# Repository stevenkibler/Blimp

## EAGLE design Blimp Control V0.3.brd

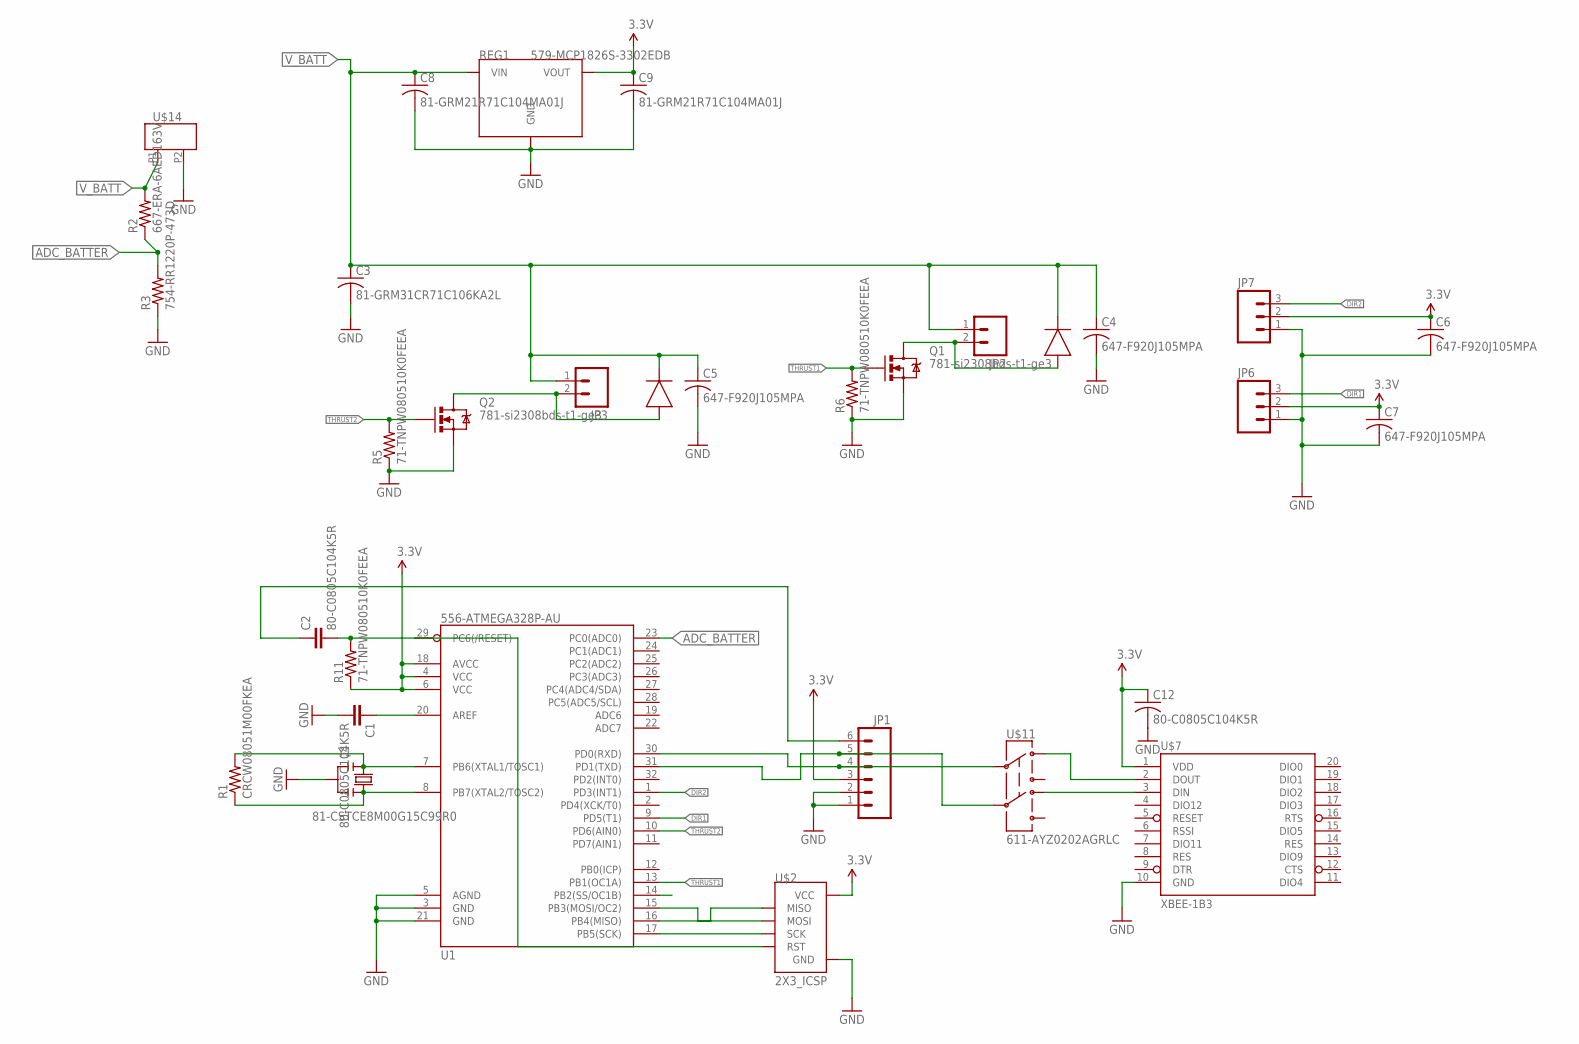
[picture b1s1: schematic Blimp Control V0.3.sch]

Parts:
C1, C2: 80-C0805C104K5R; 0805
C3: 81-GRM31CR71C106KA2L; C1206
C4, C5, C6, C7: 647-F920J105MPA; C0805
C8, C9: 81-GRM21R71C104MA01J; C0805
C12: 80-C0805C104K5R; C0805
D1, D2: 621-SBR07U20LPS-7; X2-DFN1006-2
JP1: M06LOCK; 1X06_LOCK
JP2, JP3: M02PTH; 1X02
JP6, JP7: M03LOCK; 1X03_LOCK
Q1, Q2: 781-si2308bds-t1-ge3; SOT23-3
R1: CRCW08051M00FKEA; 0805
R2: 667-ERA-6AED163V; R0805
R3: 754-RR1220P-473D; R0805
R5, R6: 71-TNPW080510K0FEEA; 0805
R11: 71-TNPW080510K0FEEA; R0805
REG1: 579-MCP1826S-3302EDB; SOT-223-3
U1: 556-ATMEGA328P-AU; TQFP32-08
U$2: 2X3_ICSP
U$7: XBEE-1B3; XBEE-SMD
U$11: 611-AYZ0202AGRLC; AYZ0202
U$14: 538-53047-0210; MOLEX_2POLE_PICO
Y1: 81-CSTCE8M00G15C99R0; RESONATOR

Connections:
3.3V: C6.1, C7.1, C9.1, C12.1, JP1.3, JP6.2, JP7.2, R11.1, REG1.3 (VOUT), U1.4 (VCC), U1.6 (VCC), U1.18 (AVCC), U$2.VCC, U$7.1 (VDD)
ADC_BATTER: R2.1, R3.2, U1.23 (PC0(ADC0))
ARDUINO_TX: JP1.5, U1.31 (PD1(TXD)), U$11.5
DIR1: JP6.3, U1.9 (PD5(T1))
DIR2: JP7.3, U1.1 (PD3(INT1))
GND: C1.2, C3.2, C4.2, C5.2, C6.2, C7.2, C8.2, C9.2, C12.2, JP1.1, JP1.2, JP6.1, JP7.1, Q1.2 (S), Q2.2 (S), R3.1, R5.1, R6.1, REG1.2 (GND), REG1.4 (GND), U1.3 (GND), U1.5 (AGND), U1.21 (GND), U$2.GND, U$7.10 (GND), U$14.P2, Y1.2
unnamed: R1.2, U1.7 (PB6(XTAL1/TOSC1)), Y1.1
unnamed: R1.1, U1.8 (PB7(XTAL2/TOSC2)), Y1.3
unnamed: C1.1, U1.20 (AREF)
unnamed: C2.2, R11.2, U1.29 (PC6(/RESET)), U$2.RST
unnamed: JP1.4, U1.30 (PD0(RXD)), U$11.2
unnamed: U1.17 (PB5(SCK)), U$2.SCK
unnamed: U1.15 (PB3(MOSI/OC2)), U$2.MOSI
unnamed: U1.16 (PB4(MISO)), U$2.MISO
unnamed: U$7.2 (DOUT), U$11.1
unnamed: C2.1, JP1.6
unnamed: U$7.3 (DIN), U$11.4
unnamed: D2.A, JP2.2, Q1.3 (D)
unnamed: D1.A, JP3.2, Q2.3 (D)
THRUST1: Q1.1 (G), R6.2, U1.13 (PB1(OC1A))
THRUST2: Q2.1 (G), R5.2, U1.10 (PD6(AIN0))
V_BATT: C3.1, C4.1, C5.1, C8.1, D1.C, D2.C, JP2.1, JP3.1, R2.2, REG1.1 (VIN), U$14.P1

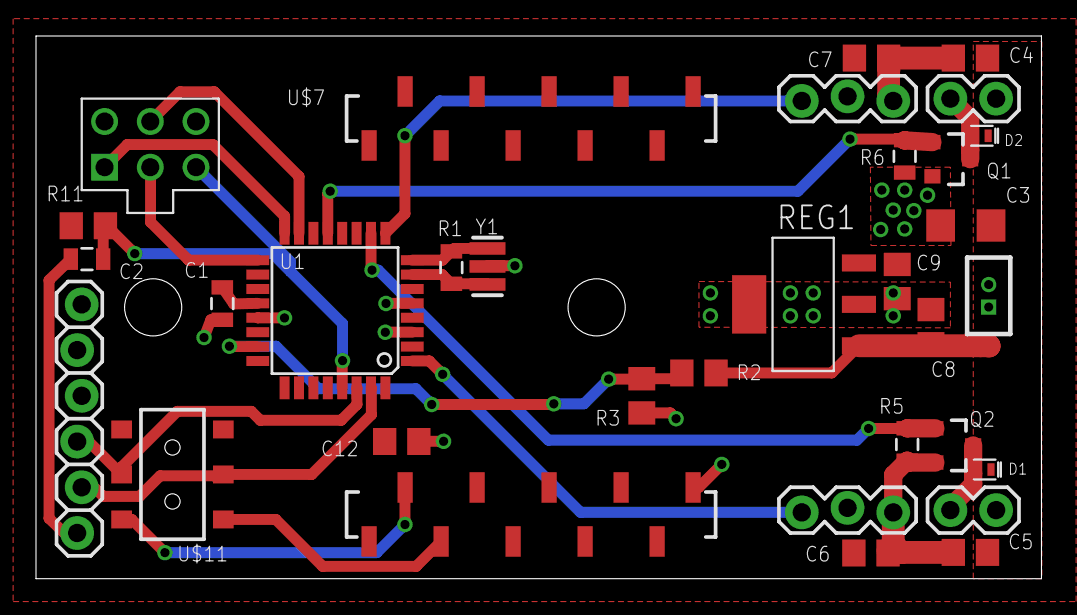
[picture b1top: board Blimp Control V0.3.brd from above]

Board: 2 copper layers, 55.9 x 30.1 mm, 32 parts (0 on the bottom side), 22 nets.

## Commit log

2015-07-05 :space_invader: Added .gitattributes & .gitignore files
2015-07-05 Joystick Code first commit
